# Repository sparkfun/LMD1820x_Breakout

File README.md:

LMD1820x Breakout
================

[
*SparkFun LMD1820x H-Bridge Breakout (BOB-00747)*](https://www.sparkfun.com/products/747)

This pcb breaks out the  the LMD18201 and LMD18200 to convenient standard 0.1" headers. 

Repository Contents
-------------------
* **/Hardware** - All Eagle design files (.brd, .sch)

License Information
-------------------
The hardware is released under [Creative Commons ShareAlike 4.0 International](https://creativecommons.org/licenses/by-sa/4.0/).

Distributed as-is; no warranty is given.

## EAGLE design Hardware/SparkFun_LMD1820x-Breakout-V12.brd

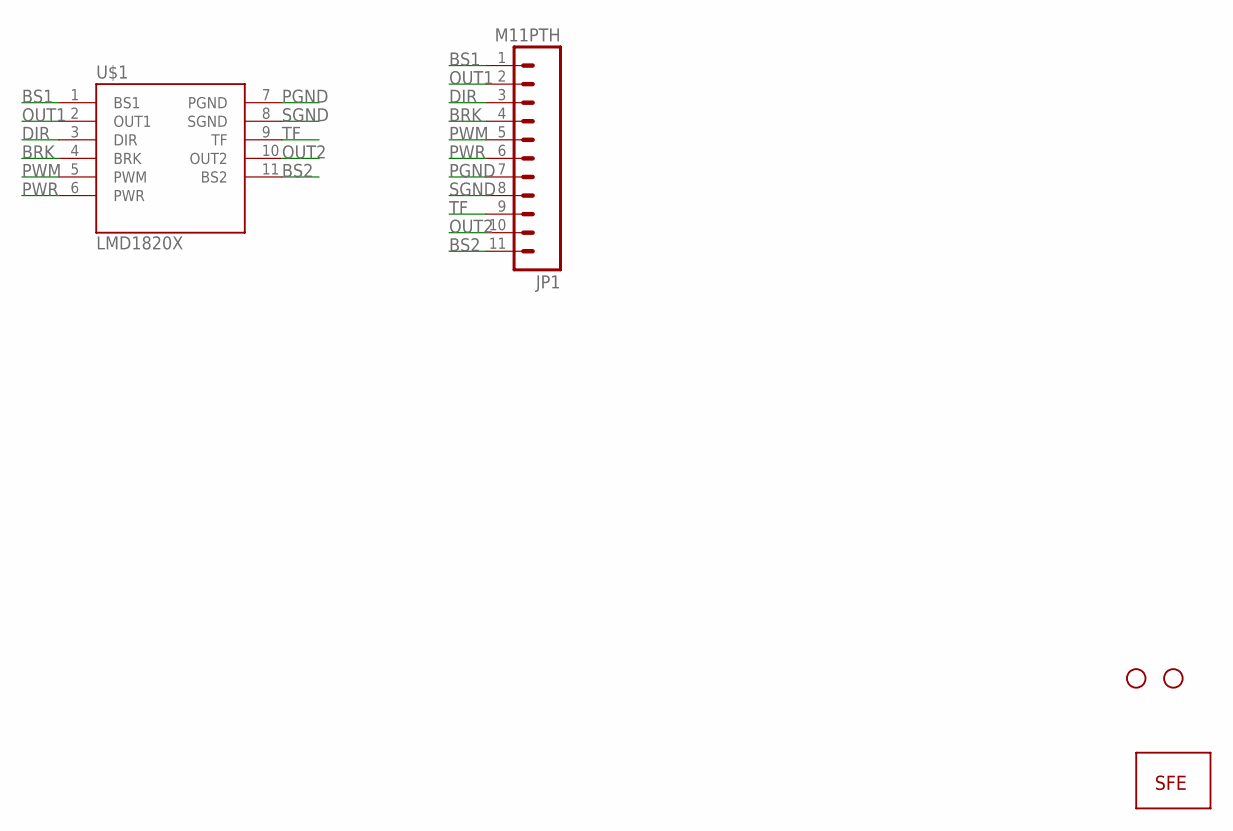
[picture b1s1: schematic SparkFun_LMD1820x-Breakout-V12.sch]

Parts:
JP1: M11PTH; 1X11
JP2, JP3: STAND-OFF
JP5: LOGO-SFENEW; SFE-NEW-WEBLOGO
U$1: LMD1820X; TO-220-11LEAD

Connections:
BRK: JP1.4, U$1.4 (BRK)
BS1: JP1.1, U$1.1 (BS1)
BS2: JP1.11, U$1.11 (BS2)
DIR: JP1.3, U$1.3 (DIR)
OUT1: JP1.2, U$1.2 (OUT1)
OUT2: JP1.10, U$1.10 (OUT2)
PGND: JP1.7, U$1.7 (PGND)
PWM: JP1.5, U$1.5 (PWM)
PWR: JP1.6, U$1.6 (PWR)
SGND: JP1.8, U$1.8 (SGND)
TF: JP1.9, U$1.9 (TF)

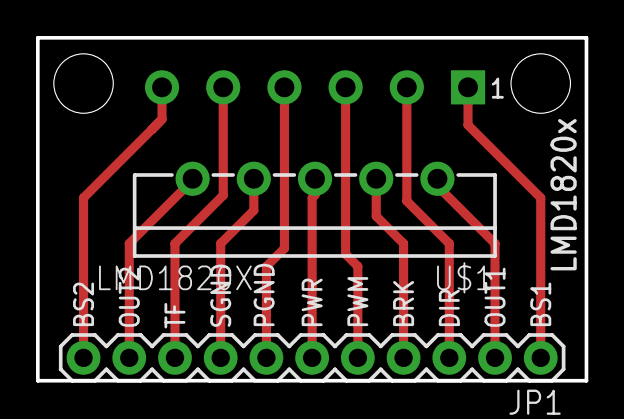
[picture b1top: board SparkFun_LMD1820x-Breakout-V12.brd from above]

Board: 2 copper layers, 30.5 x 19.1 mm, 5 parts (1 on the bottom side), 11 nets.

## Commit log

2015-01-06 Initial hardware commit
2015-01-06 Update README.md
    Adding in description.
